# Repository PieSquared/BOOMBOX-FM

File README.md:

# BOOMBOX-FM

BOOMbox is a basic fm radio with a frequency dial and on and off switch, the case is shaped like a boombox, hence why its named boombox

KiCanvas: https://kicanvas.org/?repo=https%3A%2F%2Fgithub.com%2FPieSquared%2FBOOMBOX-FM%2Ftree%2Fmain%2FPCB

## SCHEMATIC

## PCB

## PCB RENDER

## CASE

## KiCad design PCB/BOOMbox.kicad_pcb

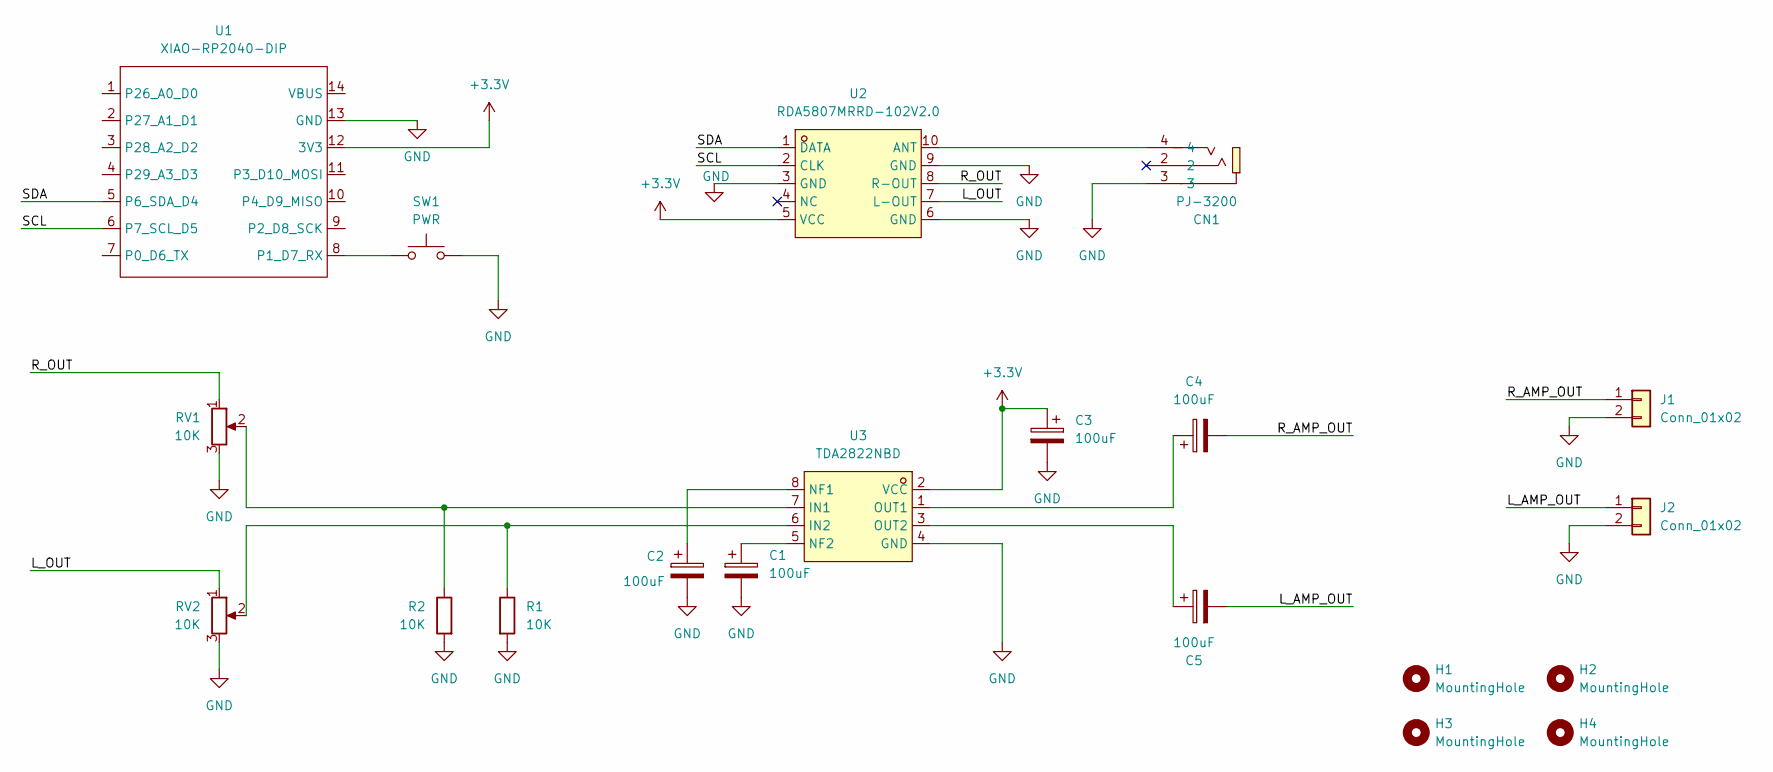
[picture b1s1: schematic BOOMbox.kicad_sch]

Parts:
C1, C2, C3, C4, C5: 100uF; CP_Radial_D6.3mm_P2.50mm
CN1: PJ-3200; AUDIO-TH_PJ-3200; MPN PJ-3200; LCSC Part C2689690
H1, H2, H3, H4: MountingHole; MountingHole_2.7mm_M2.5
J1, J2: Conn_01x02; PinHeader_1x02_P2.54mm_Vertical
R1, R2: 10K; R_Axial_DIN0207_L6.3mm_D2.5mm_P7.62mm_Horizontal
RV1, RV2: 10K; PinHeader_1x03_P2.54mm_Vertical
SW1: PWR; PinHeader_1x02_P2.54mm_Vertical
U1: XIAO-RP2040-DIP
U2: RDA5807MRRD-102V2.0; RDA5807; MPN RDA5807MRRD-102V2.0; LCSC Part C9900205627
U3: TDA2822NBD; DIP-8_W7.62mm; MPN TDA2822NBD; LCSC Part C51927337

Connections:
+3.3V: C3.1, U1.12 (3V3), U2.5 (VCC), U3.2 (VCC)
/L_AMP_OUT: C5.2, J2.1
/L_OUT: RV2.1, U2.7 (L-OUT)
/R_AMP_OUT: C4.2, J1.1
/R_OUT: RV1.1, U2.8 (R-OUT)
/SCL: U1.6 (P7_SCL_D5), U2.2 (CLK)
/SDA: U1.5 (P6_SDA_D4), U2.1 (DATA)
GND: C1.2, C2.2, C3.2, CN1.3, J1.2, J2.2, R1.2, R2.2, RV1.3, RV2.3, SW1.2, U1.13 (GND), U2.3 (GND), U2.6 (GND), U2.9 (GND), U3.4 (GND)
unnamed: SW1.1, U1.8 (P1_D7_RX)
unnamed: CN1.4, U2.10 (ANT)
unnamed: R2.1, RV1.2, U3.7 (IN1)
unnamed: R1.1, RV2.2, U3.6 (IN2)
unnamed: C2.1, U3.8 (NF1)
unnamed: C1.1, U3.5 (NF2)
unnamed: C4.1, U3.1 (OUT1)
unnamed: C5.1, U3.3 (OUT2)

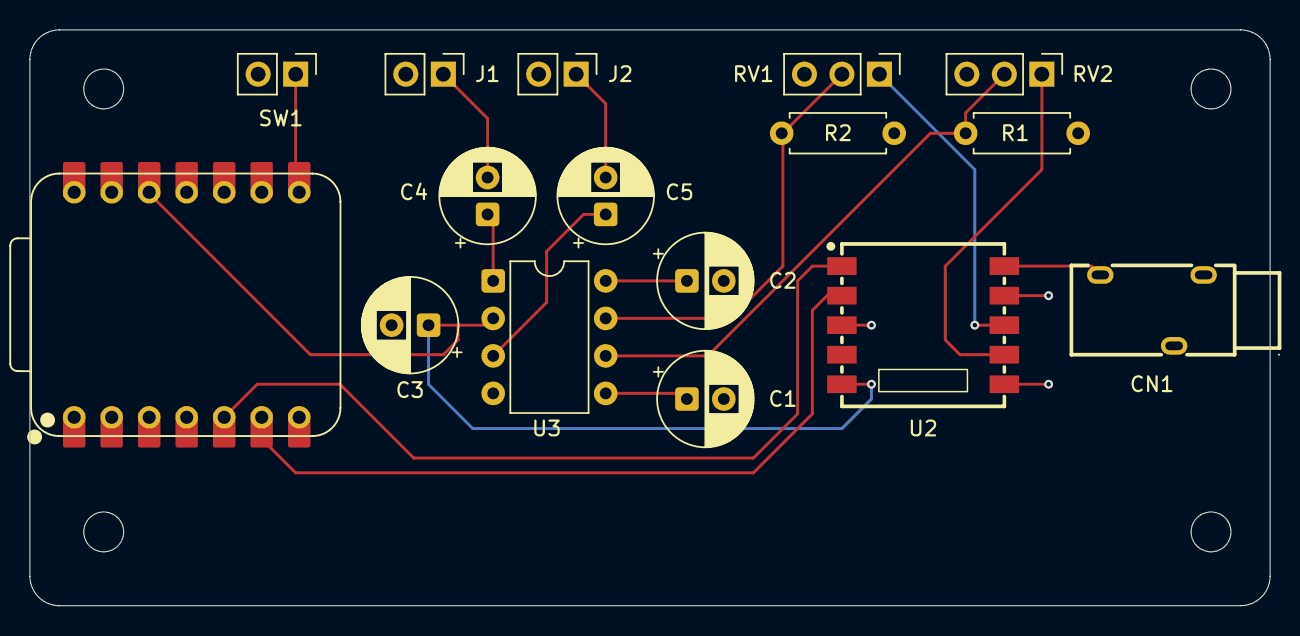
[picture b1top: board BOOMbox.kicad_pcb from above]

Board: 2 copper layers, 84.0 x 39.0 mm, 20 parts (0 on the bottom side), 16 nets.
